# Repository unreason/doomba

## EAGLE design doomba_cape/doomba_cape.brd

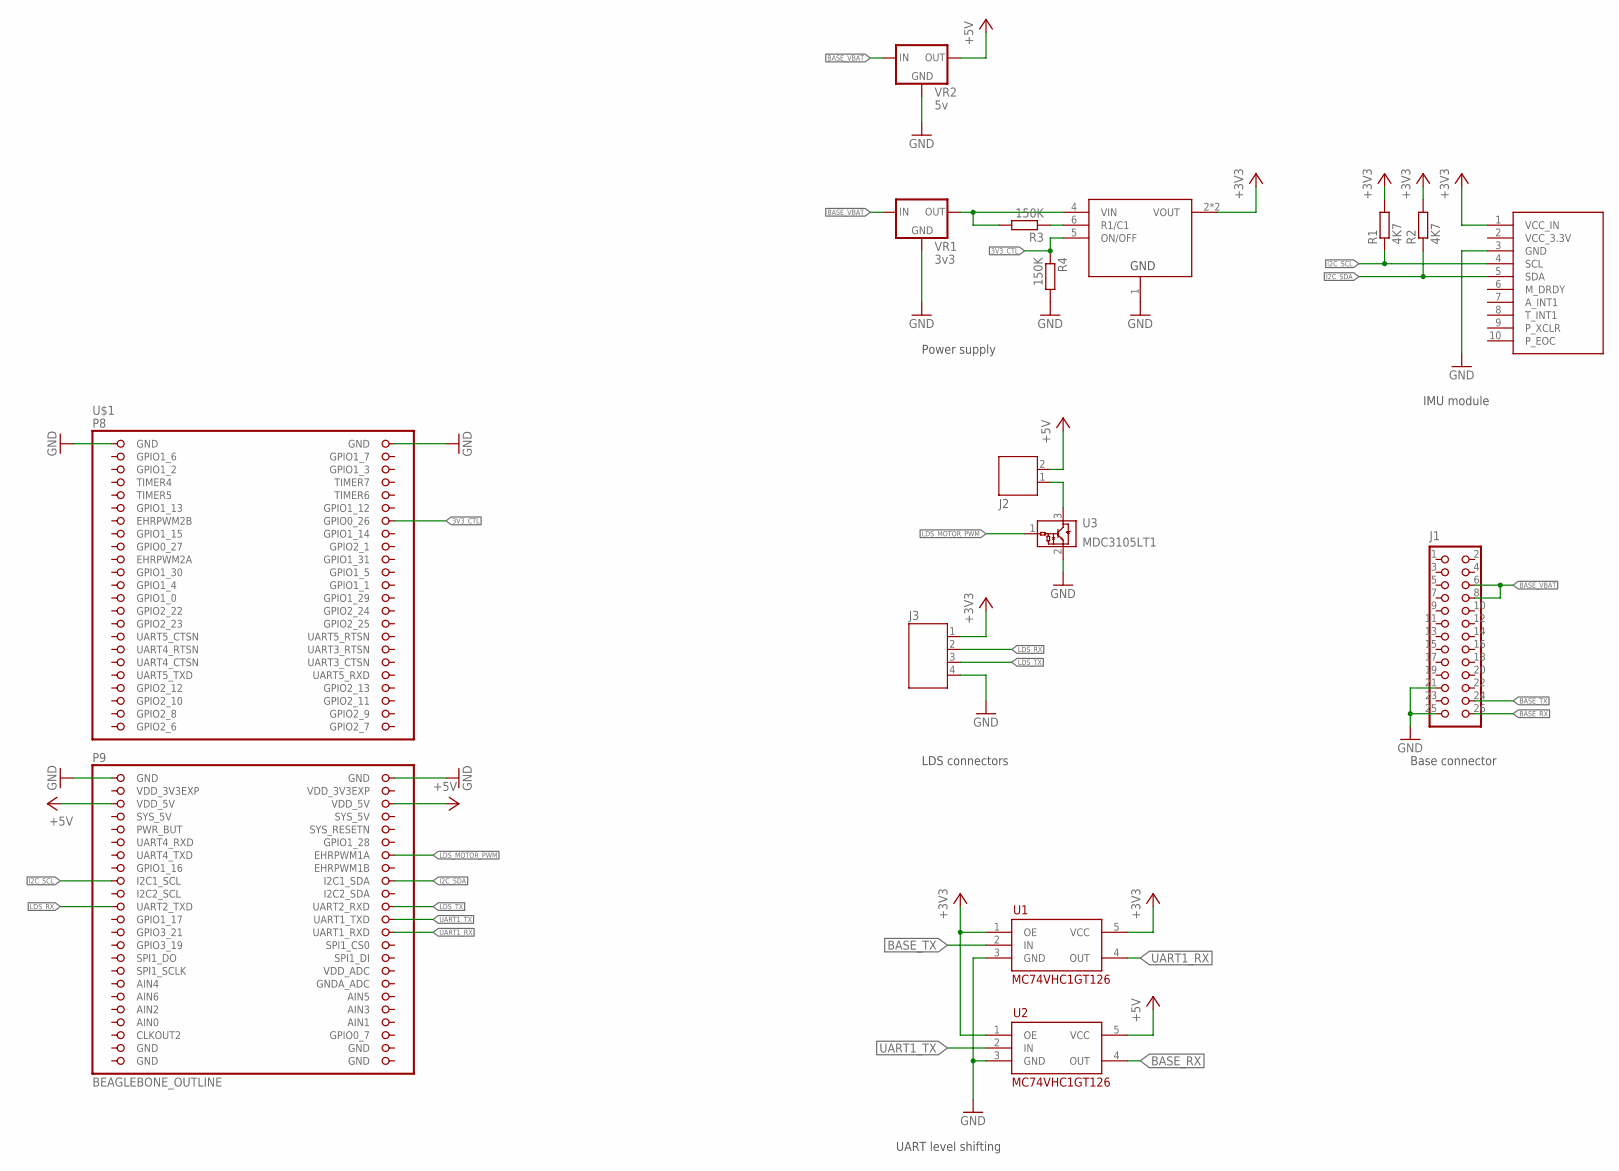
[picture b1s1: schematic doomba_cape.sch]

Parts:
J1: CONN_SHROUD_13X2; SHROUD_13X2
J2: JST-PH2
J3: JST-PH4
R1, R2: 4K7; R0603
R3, R4: 150K; R0603
U1, U2: MC74VHC1GT126; SOT-353
U3: MDC3105LT1; SOT23
U$1: BEAGLEBONE_OUTLINE; BEAGLEBONE_SHIELD
U$3: IMU-MODULE; IMU_MODULE
U$4: TPS27082L; DDC
VR1: 3v3; 2X3_90DEG
VR2: 5v; 2X3_90DEG

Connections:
3V3_CTL: R4.1, U$1.14 (GPIO0_26), U$4.5 (ON/OFF)
+3V3: J3.1, R1.2, R2.2, U1.1 (OE), U1.5 (VCC), U2.1 (OE), U$3.1 (VCC_IN), U$4.2 (VOUT), U$4.3 (VOUT)
+5V: J2.2, U2.5 (VCC), U$1.51 (VDD_5V), U$1.52 (VDD_5V), VR2.1 (OUT)
AIN0: U$1.85 (AIN0)
BASE_RX: J1.26, U2.4 (OUT)
BASE_TX: J1.24, U1.2 (IN)
BASE_VBAT: J1.6, J1.8, VR1.3 (IN), VR2.3 (IN)
GND: J1.21, J1.25, J3.4, R4.2, U1.3 (GND), U2.3 (GND), U3.2 (GND), U$1.1 (GND), U$1.2 (GND), U$1.47 (GND), U$1.48 (GND), U$1.89 (GND), U$1.90 (GND), U$1.91 (GND), U$1.92 (GND), U$3.3 (GND), U$4.1 (GND), VR1.2 (GND), VR2.2 (GND)
I2C_SCL: R1.1, U$1.63 (I2C1_SCL), U$3.4 (SCL)
I2C_SDA: R2.1, U$1.64 (I2C1_SDA), U$3.5 (SDA)
LDS_MOTOR_PWM: U3.1 (VIN), U$1.60 (EHRPWM1A)
LDS_RX: J3.2, U$1.67 (UART2_TXD)
LDS_TX: J3.3, U$1.68 (UART2_RXD)
unnamed: R3.2, U$4.4 (VIN), VR1.1 (OUT)
unnamed: R3.1, U$4.6 (R1/C1)
unnamed: J2.1, U3.3 (VOUT)
SYS_5V: U$1.53 (SYS_5V)
UART1_RX: U1.4 (OUT), U$1.72 (UART1_RXD)
UART1_TX: U2.2 (IN), U$1.70 (UART1_TXD)
VDD_3V3EXP: U$1.49 (VDD_3V3EXP), U$1.50 (VDD_3V3EXP)

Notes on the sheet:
UART level shifting
LDS connectors
Power supply
Base connector
IMU module

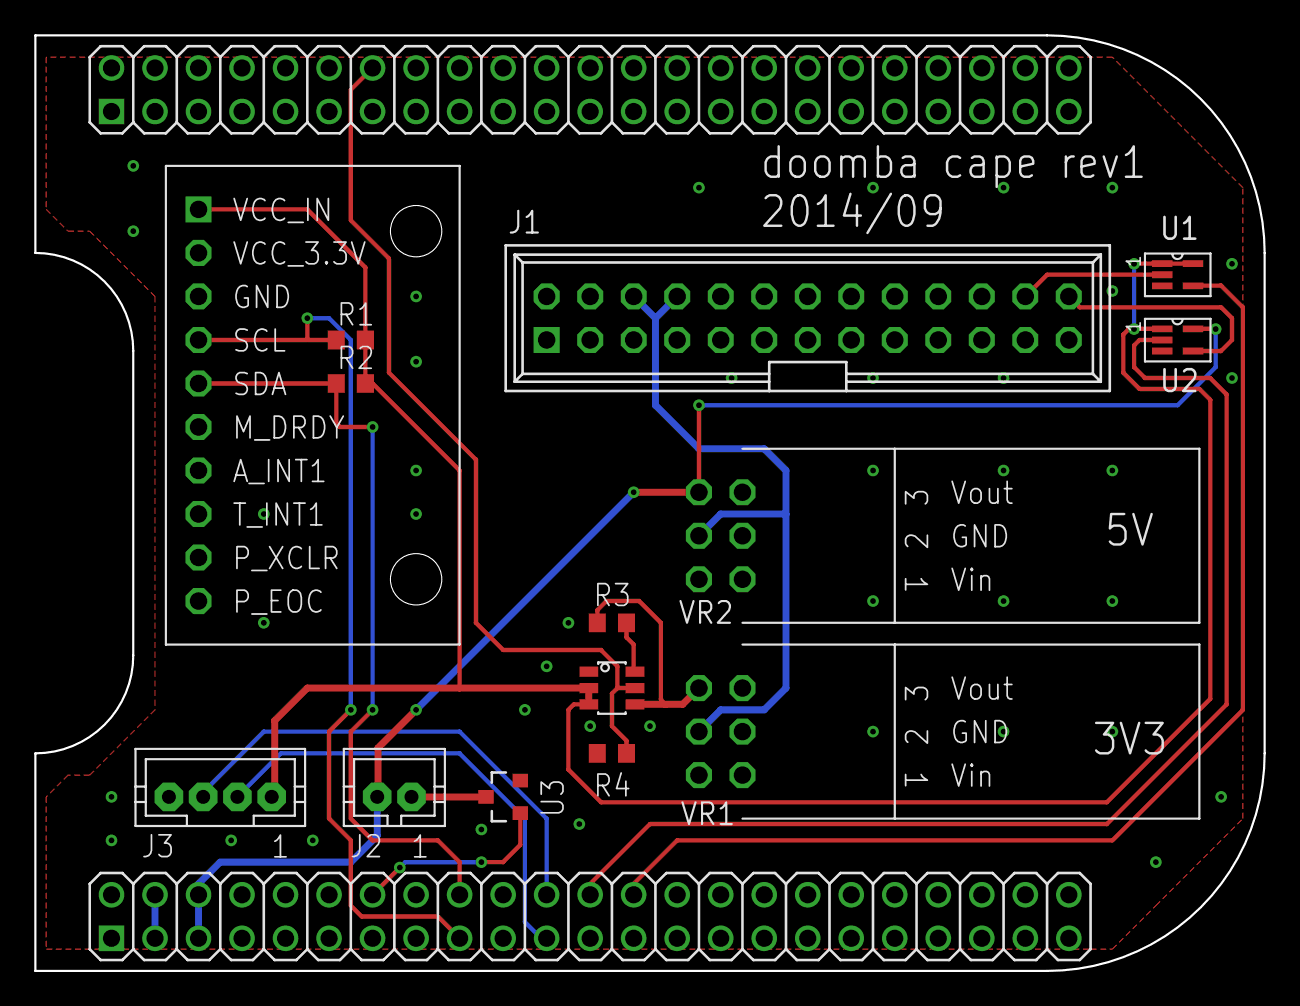
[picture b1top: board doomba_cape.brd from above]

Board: 2 copper layers, 71.8 x 54.6 mm, 15 parts (0 on the bottom side), 18 nets.

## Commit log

2014-09-11 Added a rough 3d model of the xv-11 LIDAR, and some 3rd-party models off the Web converted into the Rhino format.
2014-09-15 First shot at a mounting scheme for all the components
2014-09-15 Converted the logo from text to path
2014-09-22 BeagleBone cape - rev1 design sent to fabrication
2014-09-26 ROS configs and sources for basic Doomba bringup
